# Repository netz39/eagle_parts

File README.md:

Eagle Parts
===========

Library of components missing in [eagle](http://www.cadsoft.de/), and
some breakout boards which are almost like library parts, and some
datasheets for the previously mentioned parts …

Library Part Creation
---------------------

Help on creating parts is always welcome. After learning the basics
refer to the
[Library Management and Part Creation Standard](http://www.cadsoftusa.com/downloads/file/library_part_creation_standard.pdf)
which we also put to this repo in PDF format. For additional help see
the following links:

* http://blog.ilektronx.com/search/label/eagle%20tutorial

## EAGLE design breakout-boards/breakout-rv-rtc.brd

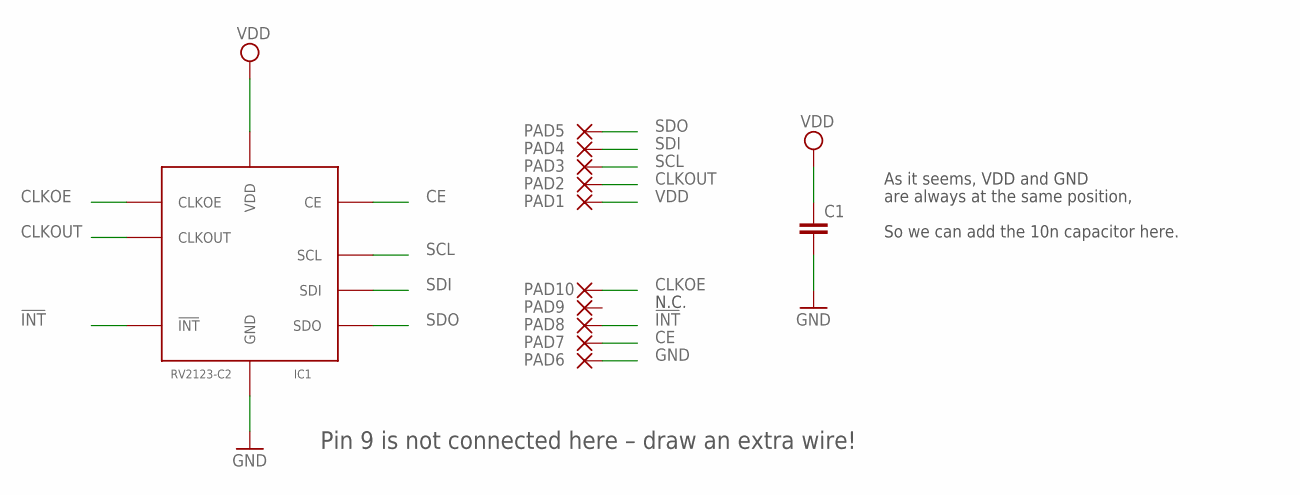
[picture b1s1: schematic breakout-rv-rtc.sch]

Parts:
C1: C-EUC0805K; C0805K
IC1: RV2123-C2; SON_10-PIN
PAD1, PAD2, PAD3, PAD4, PAD5, PAD6, PAD7, PAD8, PAD9, PAD10: 1,6/0,8

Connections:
!INT: IC1.P.8 (!INT), PAD8.1
CE: IC1.P.7 (CE), PAD7.1
CLKOE: IC1.P.10 (CLKOE), PAD10.1
CLKOUT: IC1.P.2 (CLKOUT), PAD2.1
GND: C1.2, IC1.P.6 (GND), PAD6.1
SCL: IC1.P.3 (SCL), PAD3.1
SDI: IC1.P.4 (SDI), PAD4.1
SDO: IC1.P.5 (SDO), PAD5.1
VDD: C1.1, IC1.P.1 (VDD), PAD1.1

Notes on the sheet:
N.C.
As it seems, VDD and GND
are always at the same position,
So we can add the 10n capacitor here.
Pin 9 is not connected here – draw an extra wire!

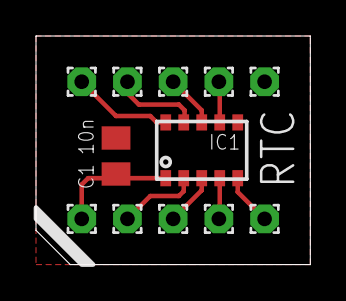
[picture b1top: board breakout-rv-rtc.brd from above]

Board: 2 copper layers, 15.2 x 12.7 mm, 12 parts (0 on the bottom side), 9 nets.

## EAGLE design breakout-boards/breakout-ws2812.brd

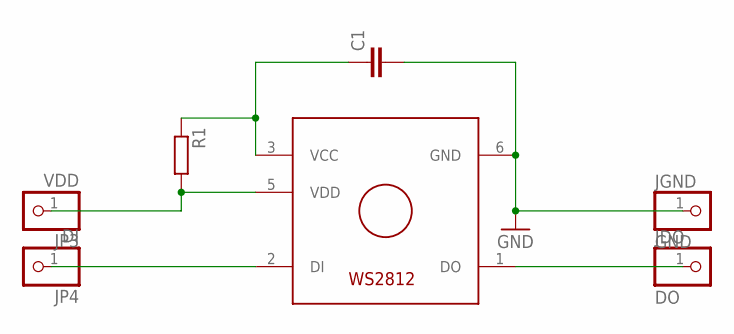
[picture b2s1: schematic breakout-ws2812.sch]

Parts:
C1: C-EUC1206; C1206
JDO: DO; 1X01
JGND: GND; 1X01
JP3: VDD; 1X01
JP4: DI; 1X01
R1: R-EU_R1206; R1206
U$1: WS2812

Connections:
GND: C1.2, JGND.1, U$1.6 (GND)
JDI: JP4.1, U$1.2 (DI)
unnamed: JDO.1, U$1.1 (DO)
VCC: C1.1, R1.1, U$1.3 (VCC)
VDD: JP3.1, R1.2, U$1.5 (VDD)

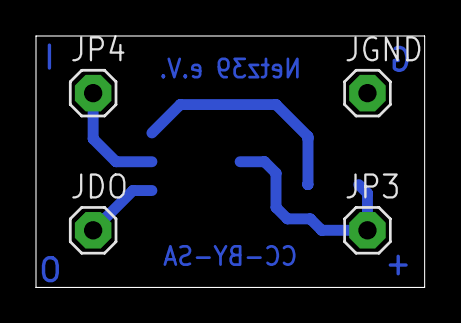
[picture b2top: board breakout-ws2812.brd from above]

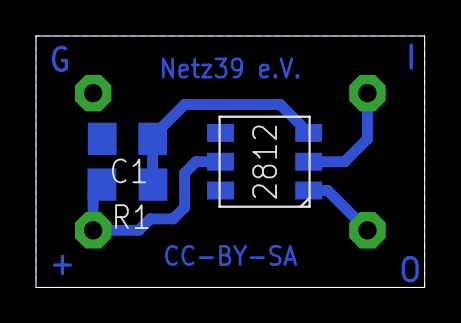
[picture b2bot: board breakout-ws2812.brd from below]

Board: 2 copper layers, 21.6 x 14.0 mm, 7 parts (3 on the bottom side), 5 nets.

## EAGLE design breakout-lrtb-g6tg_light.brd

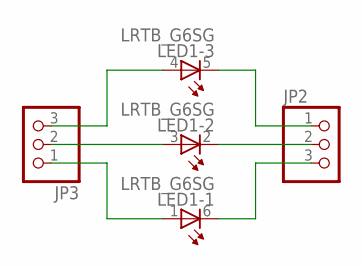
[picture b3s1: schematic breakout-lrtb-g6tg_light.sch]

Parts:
JP2, JP3: PINHD-1X3; 1X03
LED1: LRTB_G6SG

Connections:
unnamed: JP3.2, LED1.3 (A)
unnamed: JP3.3, LED1.4 (A)
unnamed: JP3.1, LED1.1 (A)
unnamed: JP2.3, LED1.6 (C)
unnamed: JP2.1, LED1.5 (C)
unnamed: JP2.2, LED1.2 (C)

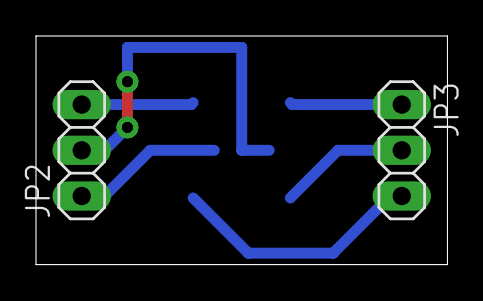
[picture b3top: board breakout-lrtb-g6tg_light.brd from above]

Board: 2 copper layers, 22.9 x 12.7 mm, 3 parts (1 on the bottom side), 6 nets.

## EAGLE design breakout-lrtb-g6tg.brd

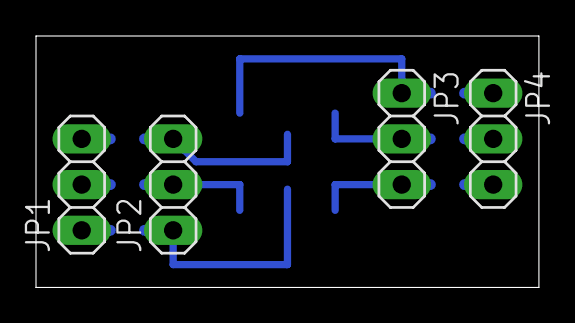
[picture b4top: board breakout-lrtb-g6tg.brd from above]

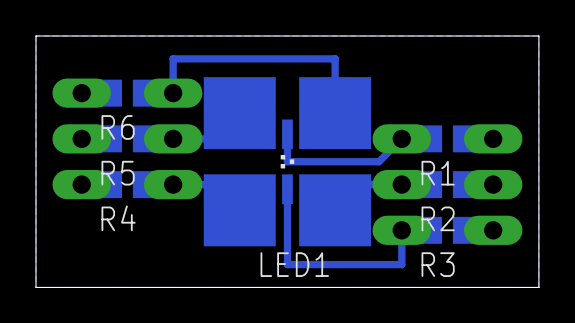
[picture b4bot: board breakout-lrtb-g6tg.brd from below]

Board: 2 copper layers, 27.9 x 14.0 mm, 11 parts (7 on the bottom side), 12 nets.

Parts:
JP1, JP2, JP3, JP4: 1X03
LED1: LRTB_G6SG
R1, R2, R3, R4, R5, R6: R0805

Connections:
unnamed: JP4.3, R4.2
unnamed: JP4.2, R5.2
unnamed: JP4.1, R6.2
unnamed: JP3.2, LED1.3, R5.1
unnamed: JP3.3, LED1.4, R4.1
unnamed: JP3.1, LED1.1, R6.1
unnamed: JP2.2, LED1.6, R2.2
unnamed: JP2.1, LED1.5, R3.2
unnamed: JP2.3, LED1.2, R1.2
unnamed: JP1.2, R2.1
unnamed: JP1.1, R3.1
unnamed: JP1.3, R1.1

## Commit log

2012-09-12 readme update
2012-09-12 initial db commit, added relais js 05 n k relais js 05 mn kt
2012-09-12 fixed some pins
2013-01-01 added WAGO connectors to library
2013-01-01 cleanup
2013-01-01 add psw 5
2013-01-02 minor fix to symbols
2013-01-02 fixed pin naming for psw_5
2013-01-28 24367dfa: fix drillhole sizes and distance
2013-01-30 another pin position fix
2013-03-03 add toggleswich and fix pads for relais
2013-03-17 Pollin RFM02 radio module
2013-03-18 RFM01 and RFM12
2013-04-20 changed solderpads on molex connector
2013-04-24 Molex-Stecker korrigiert: 5/12V vertauscht
2013-08-06 URLs in Beschreibungen gekürzt
2013-08-06 Anschlüsse für Wechselschalter angepasst
2013-08-07 add TS2940CP50
2013-08-07 add RIACON 101 and ALPS RK09K113
2013-08-07 Taster mit richtigen Maßen und neuen Pads
2013-08-12 added upright usb B connector
2013-08-31 breakout board for RGB-LED
2013-08-31 another variant just with one pin for each pad
2013-08-31 nochmal anders
2013-08-31 add text
2013-08-31 updated description
2013-09-01 add so-8 breakout board
2013-09-06 new package for soldering USB B connector
2013-09-22 add airwave awm661tx 5g8 video transmitter module
2013-09-26 add airwave awm661tx 5g8 video transmitter module
    (cherry picked from commit 876e2956514268086298c3065f4dcae5bdf7f4b6)
    Conflicts:
    n39.lbr
2013-09-26 fix automatic merge
2013-09-26 add device prefixes
2013-09-26 add ptc fuse
2013-10-12 add LM75
2013-11-09 added part for MIC4802
2013-11-09 part for WS2812
2013-11-09 adjusted port functions on MIC4802
2013-11-09 breakout-board mit Randbeschaltung für WS2812
2013-11-09 datasheets für einige Parts
2013-12-04 Eagle Part: SIL05-1A72 SIL Reed Relais
2013-12-04 Pin-Richtungen korrigiert und Beschriftung angepasst
2013-12-04 Pin-Namen angepasst
2013-12-04 move one wire away from LED solder pads
2013-12-05 Beschriftung für Bestückungsteil des Molex-Steckers korrigiert
2013-12-06 Datenblat für 1A72
2013-12-06 Datenblatt für 1A72
2013-12-06 use subdirs
2013-12-06 Added part: AVR ISP pin header
2013-12-12 Devices von Hichi integriert
2013-12-12 Description und Relais umbenannt
2013-12-17 Datenblatt IRL 540N
2013-12-17 Imported Schematic: MOSFET_N Imported Package: TO220V New Part: IRL 540N
2013-12-18 * Lötpads größer gemacht, damit sie nicht mehr abreißen * Anschluss-Beschriftung
2013-12-18 Relaisspule und 2x Wechselschalter aus relays-library importiert
2013-12-18 Part für Relais DIL M4 05H
2013-12-19 Pin-Raster korrigiert
2013-12-19 Datenblatt M405H
2013-12-19 Package DIL M4 korrigiert
2013-12-19 Überflüssiges Package entfernt
2013-12-19 Part: 2-fach Wechselrelais Package: M4 05H
2013-12-22 M4 05H: ein Pin war marginal neben dem Raster …
2013-12-22 Datenblatt ACS714
2013-12-22 Part: ACS714
2013-12-29 I³C port
2014-01-02 add AKL 59-3
2014-01-02 Schönheitskorrekturen
2014-01-02 Nubsies hinzugefügt
2014-01-02 add RIA AKL datasheets
2014-01-02 add potentiometer datasheet
2014-01-03 attiny 24/44/84 von https://github.com/chiengineer/Eagle-Libraries/tree/master/Processors/atmel
2014-01-04 I³C-Port: GND und VCC sichtbar machen (wird in Schaltbildern doch benötigt)
2014-01-06 add more packages to 2940 device (voltage regulator)
2014-01-07 added TS2940 datasheet
2014-01-13 add libs from dangerousprototypes.com
2014-01-15 Anschlussklemme RIACON 101-3 (AKL 101-03)
2014-01-15 RIACON 101-4
2014-02-17 add two USB mini connectors
2014-02-17 add USB mini connector datasheets
2014-02-19 new lib for good (muha!) ATtiny/ATmega packages (starting with ATtiny25/45/85 in 4 packages)
2014-02-21 moved some pins around in symbol, proposed in #40
2014-02-25 Description, Title and Data Sheet for JS-Relais * JS_05_MN_KT * JS_05_N_K
2014-02-25 Aussagekräftige Bezeichnung für PSW5 Part umbenannt: * PWS_5 -> MOLEX_8981
2014-02-26 improve GND pins of symbol and package PSW_5
2014-03-01 DC Power Jack for Reichelt HEBO13
    Adding
    * part DC_JACK
    * package DC_JACK_HEBO13
    * symbol DC_JACK
2014-03-02 Symbol DC_JACK: Direction auf »pas« (passive)
2014-03-02 Added SENSE output to DC Jack, affected parts: * part DC_JACK * package DC_JACK_HEBO13 * symbol DC_JACK
2014-03-02 Re-use existing DC-JACK from con-jack.
    Affected parts:
    * sym DC_JACK
    * sym JACK-PLUG
    * part DC_JACK
2014-03-02 Package DC_JACK_HEBO13: adjusted solder pads
2014-03-05 Copied part SRKL from switch-misc for adaptation.
2014-03-05 Copy notice for part SRKL.
2014-03-05 package SRKL: rotate the switch pins to solve DRC overlap warnings.
2014-03-06 add datasheet for SMD PTC fuse
2014-03-06 rename device SIBA_194600 to PTC-FUSE and add metadata
    this is a preparation for adding more packages to this new generic PTC
    fuse device
2014-03-06 add datasheets and adapt device description
2014-03-06 add LP60-050 package for PTC fuse
2014-04-12 Corrected the WS2812 PIN definition.
2014-04-12 Adapted to corrected WS2812 pin layout (moved one GND connection)
2014-04-21 Copied NE555 from st-microelectronics.lbr for further changes.
2014-04-21 NE555: Named existing variant "DIL"
2014-04-21 NE555: Added SO08 variant.
2014-04-21 NE555: Descriptions and Reichelt part numbers
2014-04-21 1N4841: Variant from diode.lbr with SMD package SOD-80
2014-04-25 added first flag to dil-08 pin 1
2014-04-25 changed ne555 discharge pin to open collector
2014-04-27 ws2812: moved things around to center package
2014-04-27 move board dimension to origin, update ws2812 package, reroute
    The lower left corner of the board dimension was not coincident with the
    coordinates 0,0 which lead to difficulties moving an exported dxf to the
    right place for drilling/milling, so I moved everything an half inch to
    the right. Then I used the new centered ws2812 package and routed the
    wires again. The drills are still in place, but next time the board is
    slightly different.
2014-05-03 ACS714: changed part prefix to "IC"
2014-05-03 ASC714: corrected the device name
2014-05-04 ACS714: Introduced an adapted package that combines the IP+/- pins to common solder pads for better routing.
2014-06-28 WS2812: better symbol
    Restructured the symbol so that chains can be easier modelled in the schematic.
2014-11-30 DS1307: added device (RTC)
2014-12-29 ds1307: moved pins around in symbol as discussed in PR
2015-02-16 MCP9808: Data Sheet
2015-02-16 MSOP8: from ref-packages.lbr
2015-02-16 MCP9808
2015-02-17 MCP9808: Pin-Typen angepasst
    * Alarm → out
    * A0…A2 → in
2015-05-04 FT232H Data Sheet
    Do not confuse the FT232H with other ICs from the FT232 series!
    More on the FT232H on http://www.ftdichip.com/Products/ICs/FT232H.htm
2015-05-04 Add LQFP-48 package
    from the SparkFun libraries, needed for the FT232H
2015-05-04 FT232H Eagle Part
2015-05-05 Add LQFP48 package
    from the Eagle ref-packages library, needed for the FT232H
2015-11-29 DS1307Z: move X2 one grid step to the right
    ---
    this looks nicer when actually attaching a crystal in schematic
2015-12-06 Knopfzellenhalter (KZH) hinzugefügt
    Device ist KZH, um später andere Größen als weitere Packages hinzufügen
    zu können, Package ist erstmal nur eins als KZH20 drin, was dem KZH 20-1
    bei Reichelt [1] entspricht und ggf. noch ergänzt werden muss. Das
    Symbol ist ein 1V2 aus der eagle Library "battery" übernommen.
    [1] https://secure.reichelt.de/?ARTICLE=44621
2015-12-06 add datasheet for KZH20
2015-12-13 KZH: adapted drill diameter, added descriptions and links
2015-12-13 RV 2123-C2: Data Sheets
2015-12-13 Add SON 10-pin Eagle package
    See data sheet for RV 2123-C2 for details on the package.
2015-12-13 RV 2123-C2: Eagle symbol
2015-12-13 RV 2123-C2: Eagle part
2015-12-14 added some help for creating and reviewing library parts
2015-12-14 SON 10-pin: Correct measurements
2015-12-14 RV 2123-C2 symbol: adjusted pin names/classification
2015-12-15 add prefix to device KZH (as in eagle library battery)
2015-12-15 kzh: improve package
    * outline now 8mil
    * moved some stuff away from tPlace layer to not appear on silkscreen
    * added + and - signs for reference
2015-12-20 RV 2123-C2: Do not show pad names
    Solves issue #61
2015-12-20 RV 2123-C2: Change prefix to "IC"
2015-12-27 Eagle Part for GoldCaps
    with a package for https://www.reichelt.de/index.html?&ARTICLE=111711
2015-12-27 Add package for 16.3mm high caps
    such as found in https://www.reichelt.de/index.html?&ARTICLE=111711
2015-12-27 Transfer the symbol "CPOL" from restistor library
2015-12-29 Tidy up the links
    Make the links active and directly link to the DataSheep in Reichelt CDN.
2015-12-29 Breakout Board for RV RTC modules
    As it seems, VCC and GND are always at pins 1 and 6, so the 10nF capacity can be included. :)

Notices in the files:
breakout-boards/breakout-rv-rtc.brd:
CC BY-SA Netz39
breakout-boards/breakout-ws2812.brd:
CC-BY-SA
